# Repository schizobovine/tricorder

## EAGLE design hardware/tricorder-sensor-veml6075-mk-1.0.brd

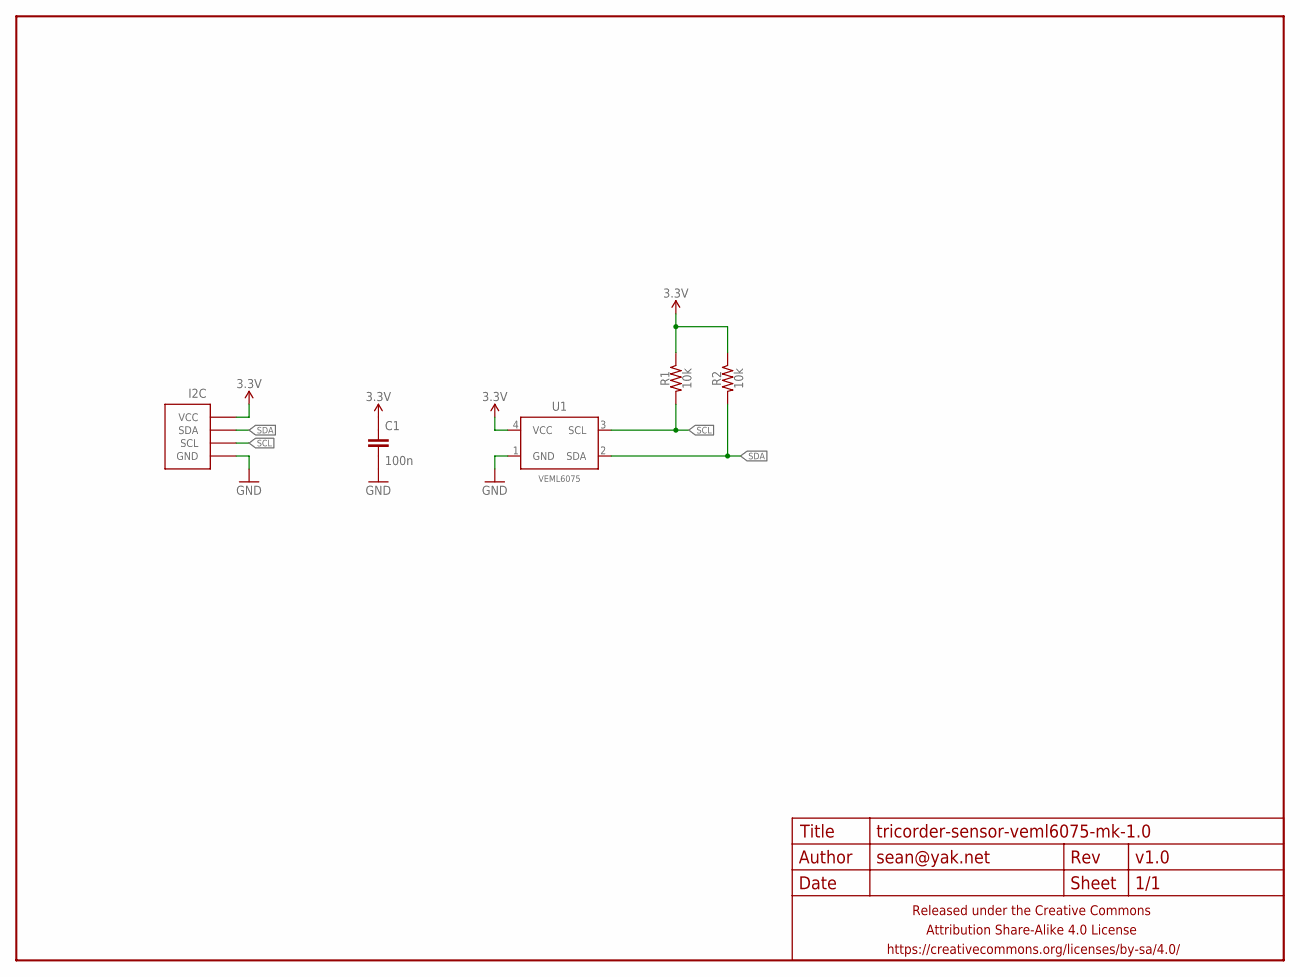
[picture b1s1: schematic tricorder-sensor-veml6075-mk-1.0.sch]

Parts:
C1: 100n; C0603
FRAME1: FRAME-LETTERNO_PACKAGE; DUMMY
I2C: M04-I2CPTH-0.1IN-CENTERED; 1X04-PTH-VERT-I2C-CENTERED
R1, R2: 10k; R0603
U1: VEML6075; OPLGA4

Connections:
3.3V: C1.1, I2C.VCC, R1.1, R2.1, U1.4 (VCC)
GND: C1.2, I2C.GND, U1.1 (GND)
SCL: I2C.SCL, R1.2, U1.3 (SCL)
SDA: I2C.SDA, R2.2, U1.2 (SDA)

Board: 2 copper layers, 6 parts (2 on the bottom side), 4 nets, no tracks yet.

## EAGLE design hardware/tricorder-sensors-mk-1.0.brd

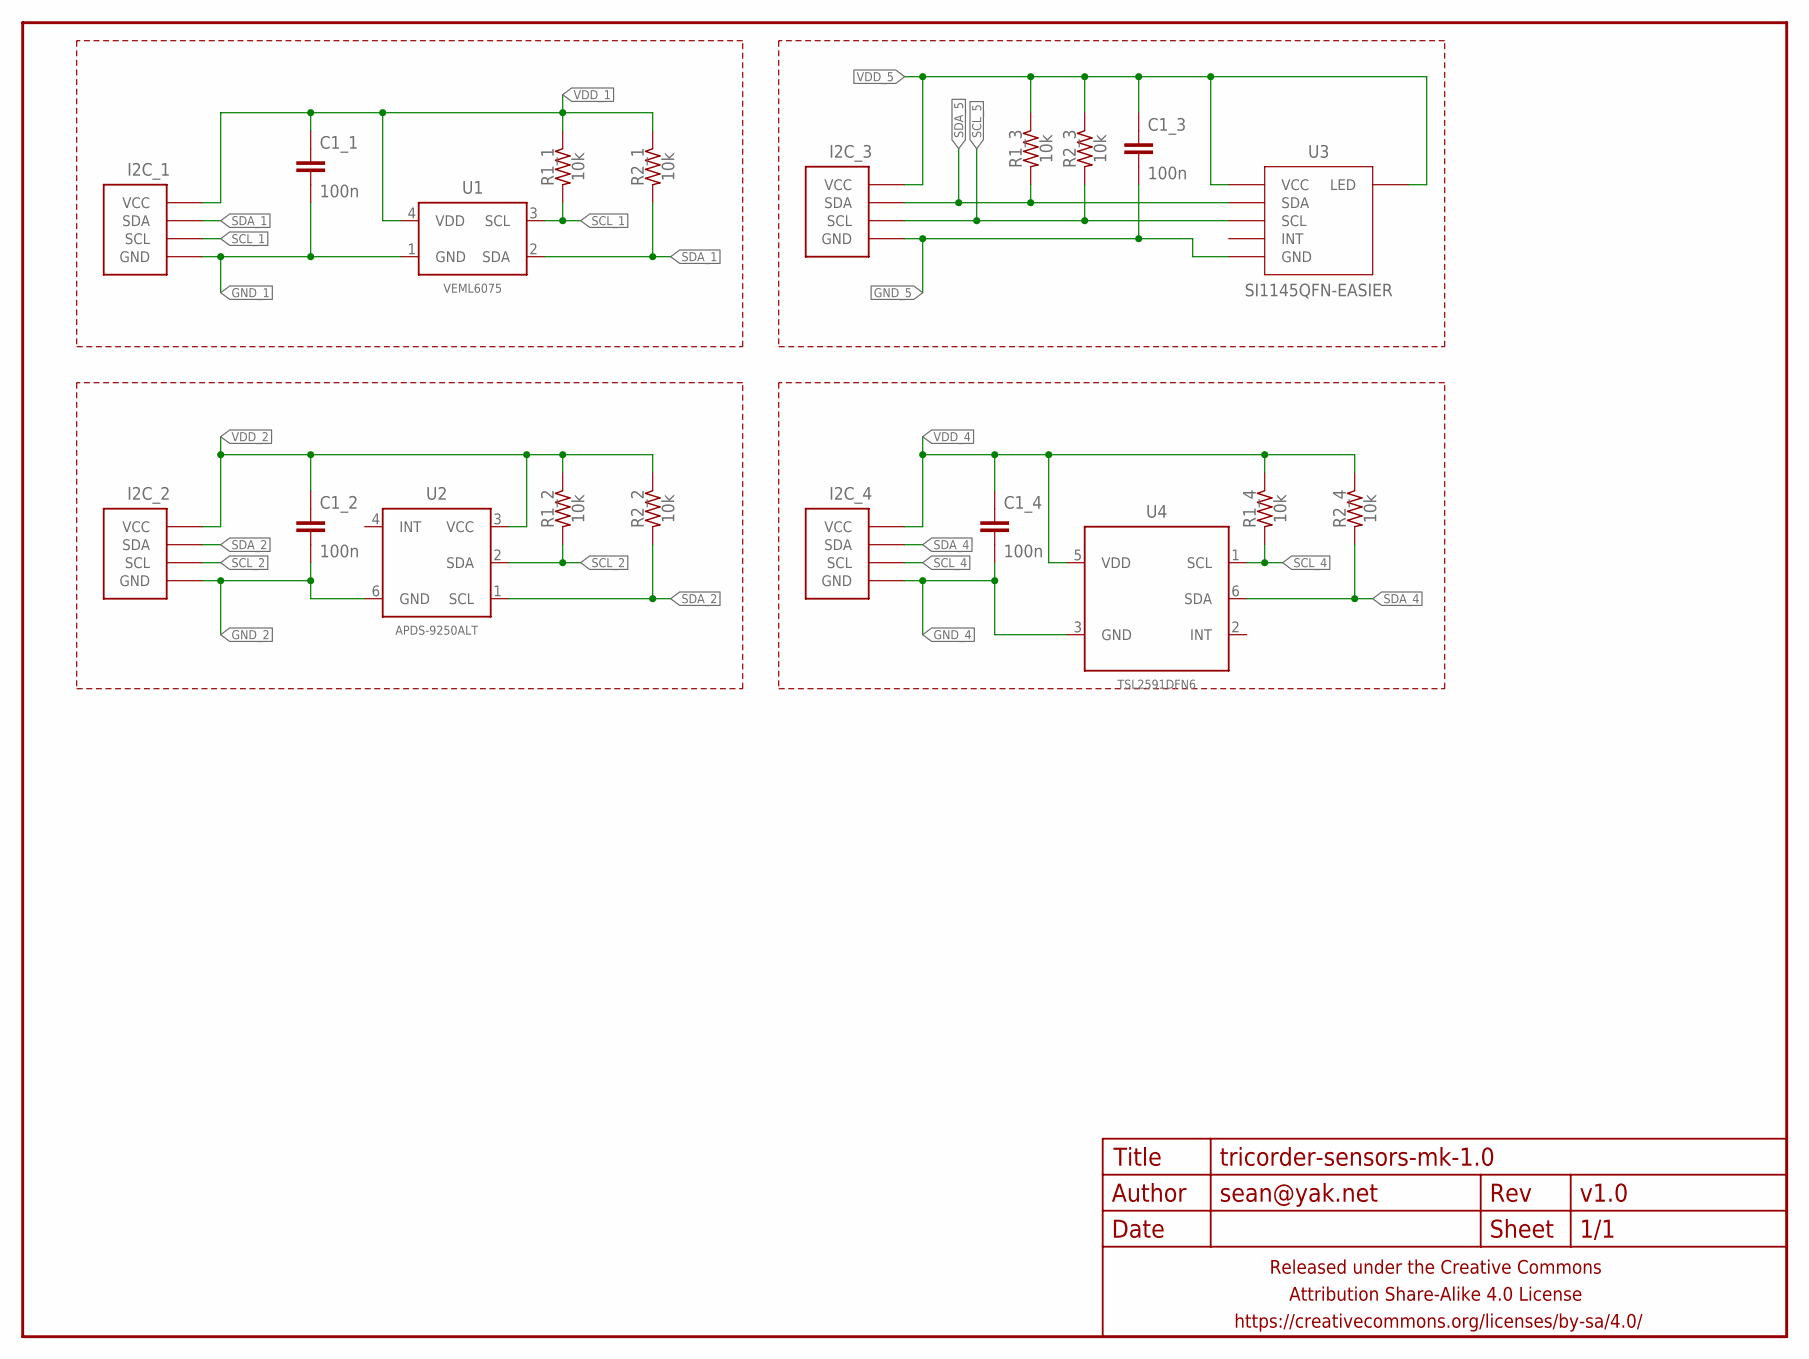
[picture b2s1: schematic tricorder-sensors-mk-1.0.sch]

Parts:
C1_1, C1_2, C1_3, C1_4: 100n; C0603
FRAME1: FRAME-LETTERNO_PACKAGE; DUMMY
I2C_1, I2C_2, I2C_3, I2C_4: M04-I2CPTH-0.1IN-CENTERED; 1X04-PTH-VERT-I2C-CENTERED
R1_1, R1_2, R1_3, R1_4, R2_1, R2_2, R2_3, R2_4: 10k; R0603
U1: VEML6075; OPLGA4
U2: APDS-9250ALT; APDS-9250-ALT
U3: SI1145QFN-EASIER; SI1145-ALT
U4: TSL2591DFN6; TSL2951_DFN6

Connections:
GND_1: C1_1.2, I2C_1.GND, U1.1 (GND)
GND_2: C1_2.2, I2C_2.GND, U2.6 (GND)
GND_4: C1_4.2, I2C_4.GND, U4.3 (GND)
GND_5: C1_3.2, I2C_3.GND, U3.GND
SCL_1: I2C_1.SCL, R1_1.2, U1.3 (SCL)
SCL_2: I2C_2.SCL, R1_2.2, U2.2 (SDA)
SCL_4: I2C_4.SCL, R1_4.2, U4.1 (SCL)
SCL_5: I2C_3.SCL, R2_3.2, U3.SCL
SDA_1: I2C_1.SDA, R2_1.2, U1.2 (SDA)
SDA_2: I2C_2.SDA, R2_2.2, U2.1 (SCL)
SDA_4: I2C_4.SDA, R2_4.2, U4.6 (SDA)
SDA_5: I2C_3.SDA, R1_3.2, U3.SDA
VDD_1: C1_1.1, I2C_1.VCC, R1_1.1, R2_1.1, U1.4 (VDD)
VDD_2: C1_2.1, I2C_2.VCC, R1_2.1, R2_2.1, U2.3 (VCC)
VDD_4: C1_4.1, I2C_4.VCC, R1_4.1, R2_4.1, U4.5 (VDD)
VDD_5: C1_3.1, I2C_3.VCC, R1_3.1, R2_3.1, U3.LED, U3.VCC@1 (VCC), U3.VCC@2 (VCC)

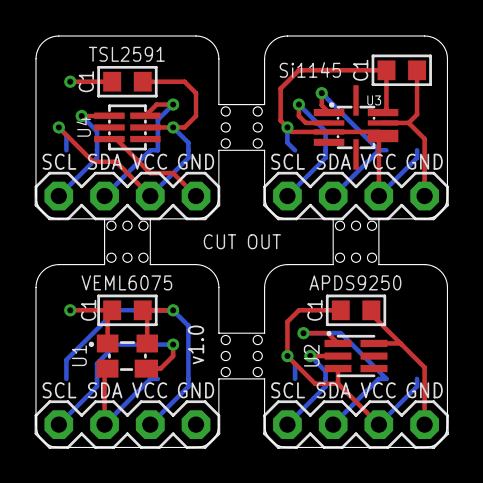
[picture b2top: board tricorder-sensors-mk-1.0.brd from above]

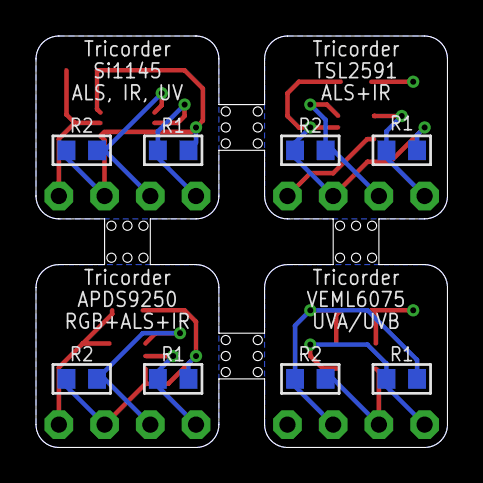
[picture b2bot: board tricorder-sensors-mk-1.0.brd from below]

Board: 2 copper layers, 22.9 x 22.9 mm, 21 parts (8 on the bottom side), 16 nets.

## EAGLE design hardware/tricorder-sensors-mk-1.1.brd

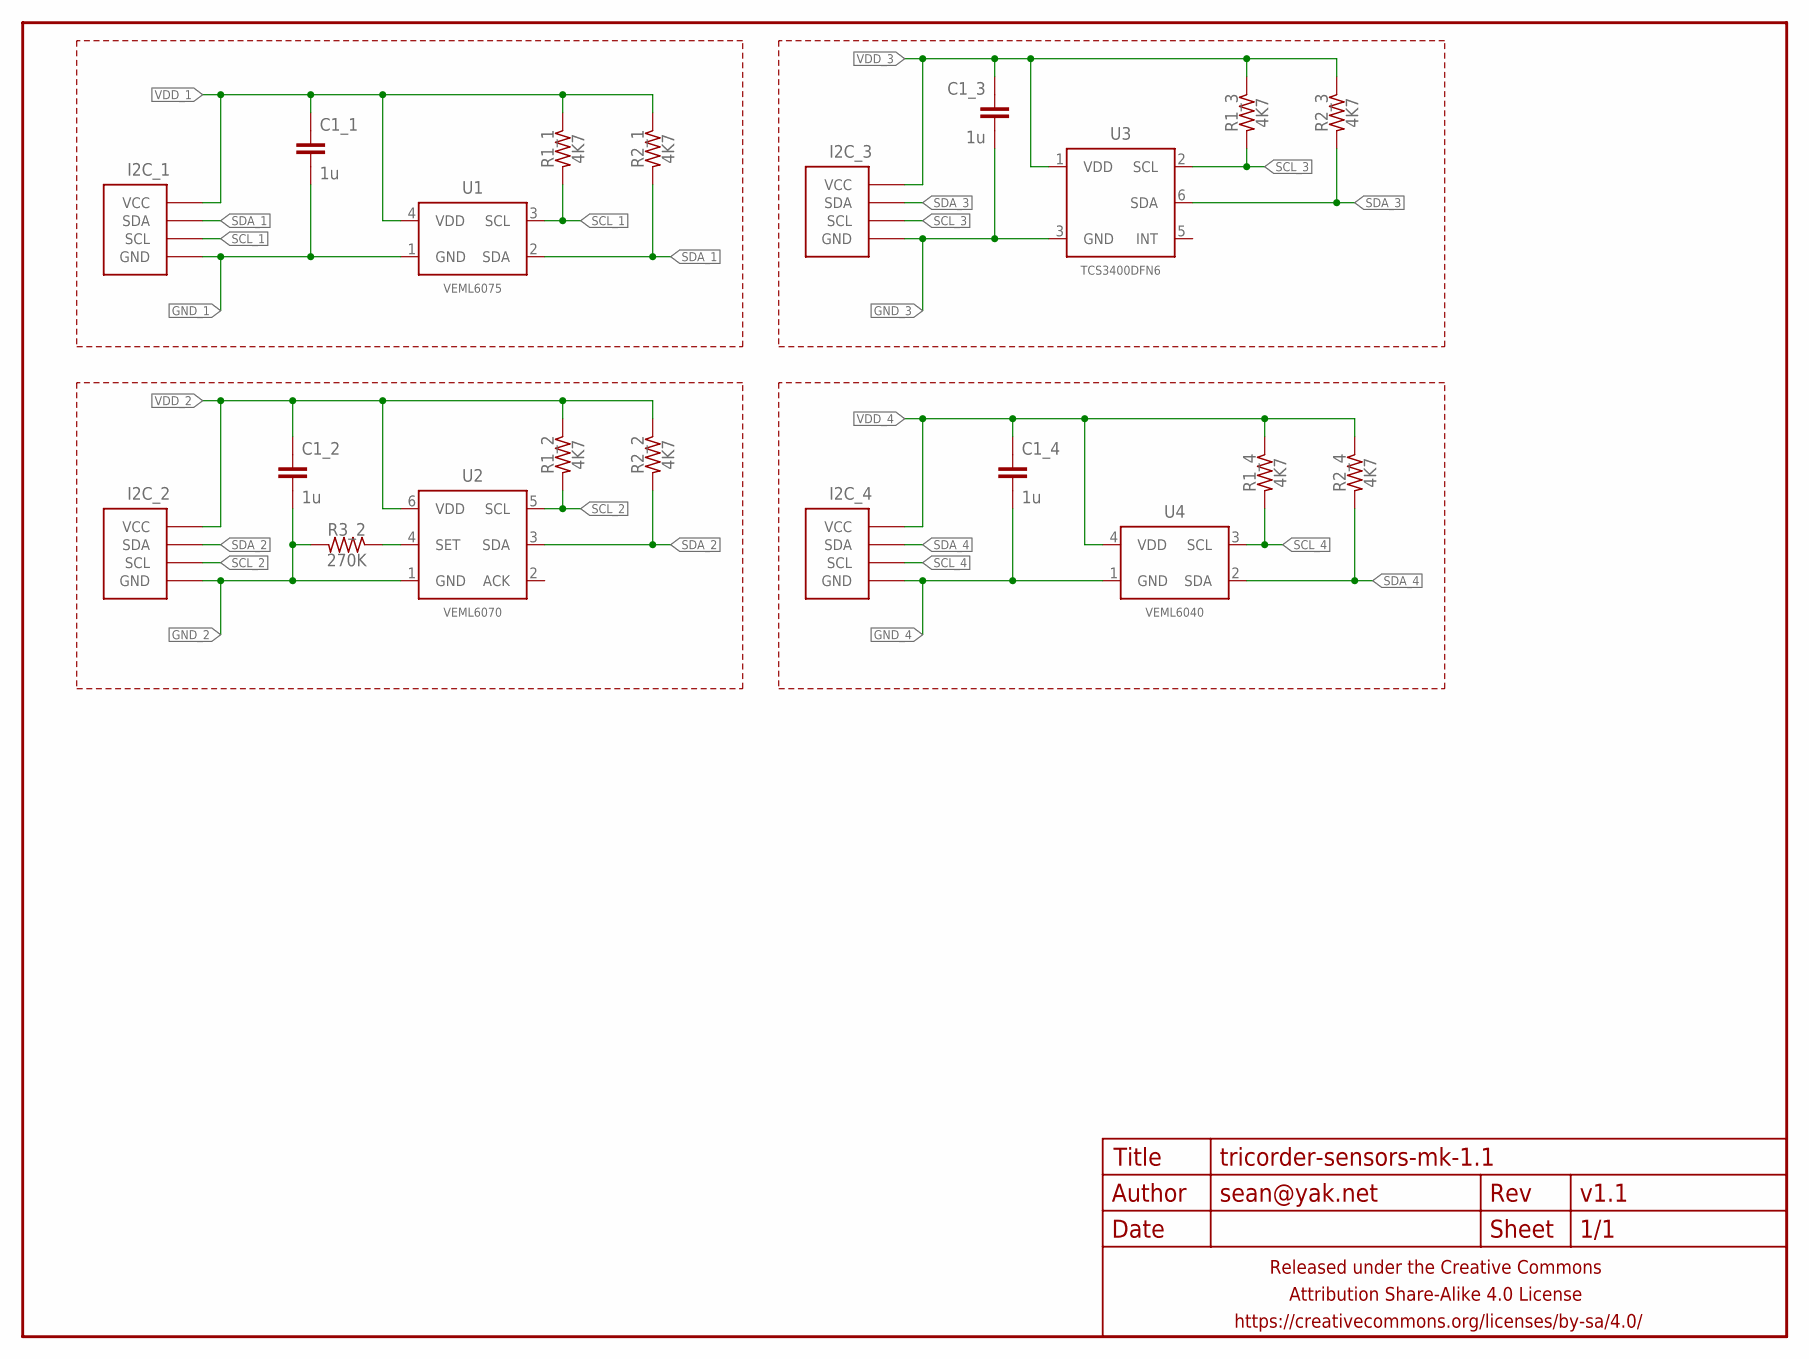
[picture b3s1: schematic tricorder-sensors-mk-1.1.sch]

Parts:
C1_1, C1_2, C1_3, C1_4: 1u; C0603
FRAME1: FRAME-LETTERNO_PACKAGE; DUMMY
I2C_1, I2C_2, I2C_3, I2C_4: M04-I2CPTH-0.1IN-CENTERED; 1X04-PTH-VERT-I2C-CENTERED
R1_1, R1_2, R1_3, R1_4, R2_1, R2_2, R2_3, R2_4: 4K7; R0603
R3_2: 270K; R0603
U1: VEML6075; OPLGA4
U2: VEML6070; OPLGA6
U3: TCS3400DFN6; TCS3400_DFN6
U4: VEML6040; OPLGA4

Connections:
GND_1: C1_1.2, I2C_1.GND, U1.1 (GND)
GND_2: C1_2.2, I2C_2.GND, R3_2.2, U2.1 (GND)
GND_3: C1_3.2, I2C_3.GND, U3.3 (GND)
GND_4: C1_4.2, I2C_4.GND, U4.1 (GND)
unnamed: R3_2.1, U2.4 (SET)
SCL_1: I2C_1.SCL, R1_1.2, U1.3 (SCL)
SCL_2: I2C_2.SCL, R1_2.2, U2.5 (SCL)
SCL_3: I2C_3.SCL, R1_3.2, U3.2 (SCL)
SCL_4: I2C_4.SCL, R1_4.2, U4.3 (SCL)
SDA_1: I2C_1.SDA, R2_1.2, U1.2 (SDA)
SDA_2: I2C_2.SDA, R2_2.2, U2.3 (SDA)
SDA_3: I2C_3.SDA, R2_3.2, U3.6 (SDA)
SDA_4: I2C_4.SDA, R2_4.2, U4.2 (SDA)
VDD_1: C1_1.1, I2C_1.VCC, R1_1.1, R2_1.1, U1.4 (VDD)
VDD_2: C1_2.1, I2C_2.VCC, R1_2.1, R2_2.1, U2.6 (VDD)
VDD_3: C1_3.1, I2C_3.VCC, R1_3.1, R2_3.1, U3.1 (VDD)
VDD_4: C1_4.1, I2C_4.VCC, R1_4.1, R2_4.1, U4.4 (VDD)

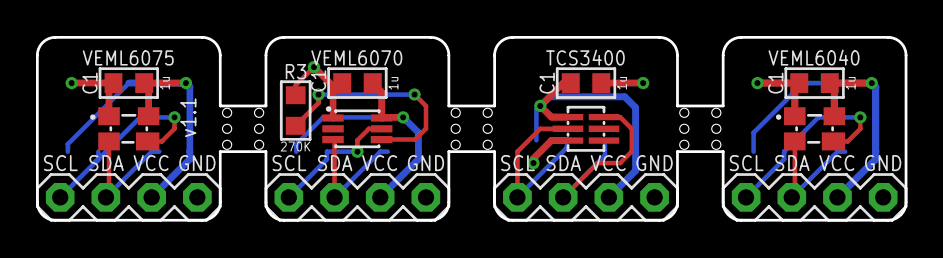
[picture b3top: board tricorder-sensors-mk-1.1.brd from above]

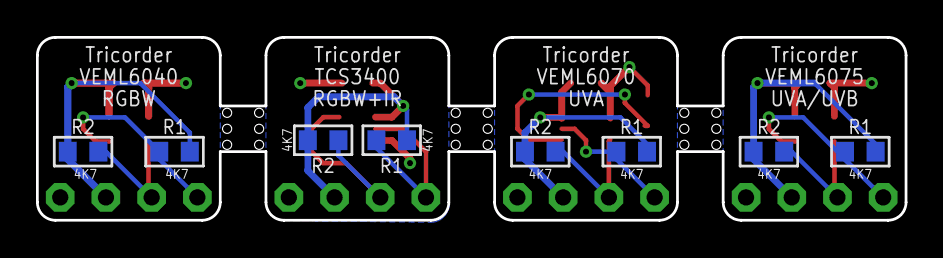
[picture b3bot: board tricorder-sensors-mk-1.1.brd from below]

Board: 2 copper layers, 48.3 x 10.2 mm, 22 parts (8 on the bottom side), 17 nets.

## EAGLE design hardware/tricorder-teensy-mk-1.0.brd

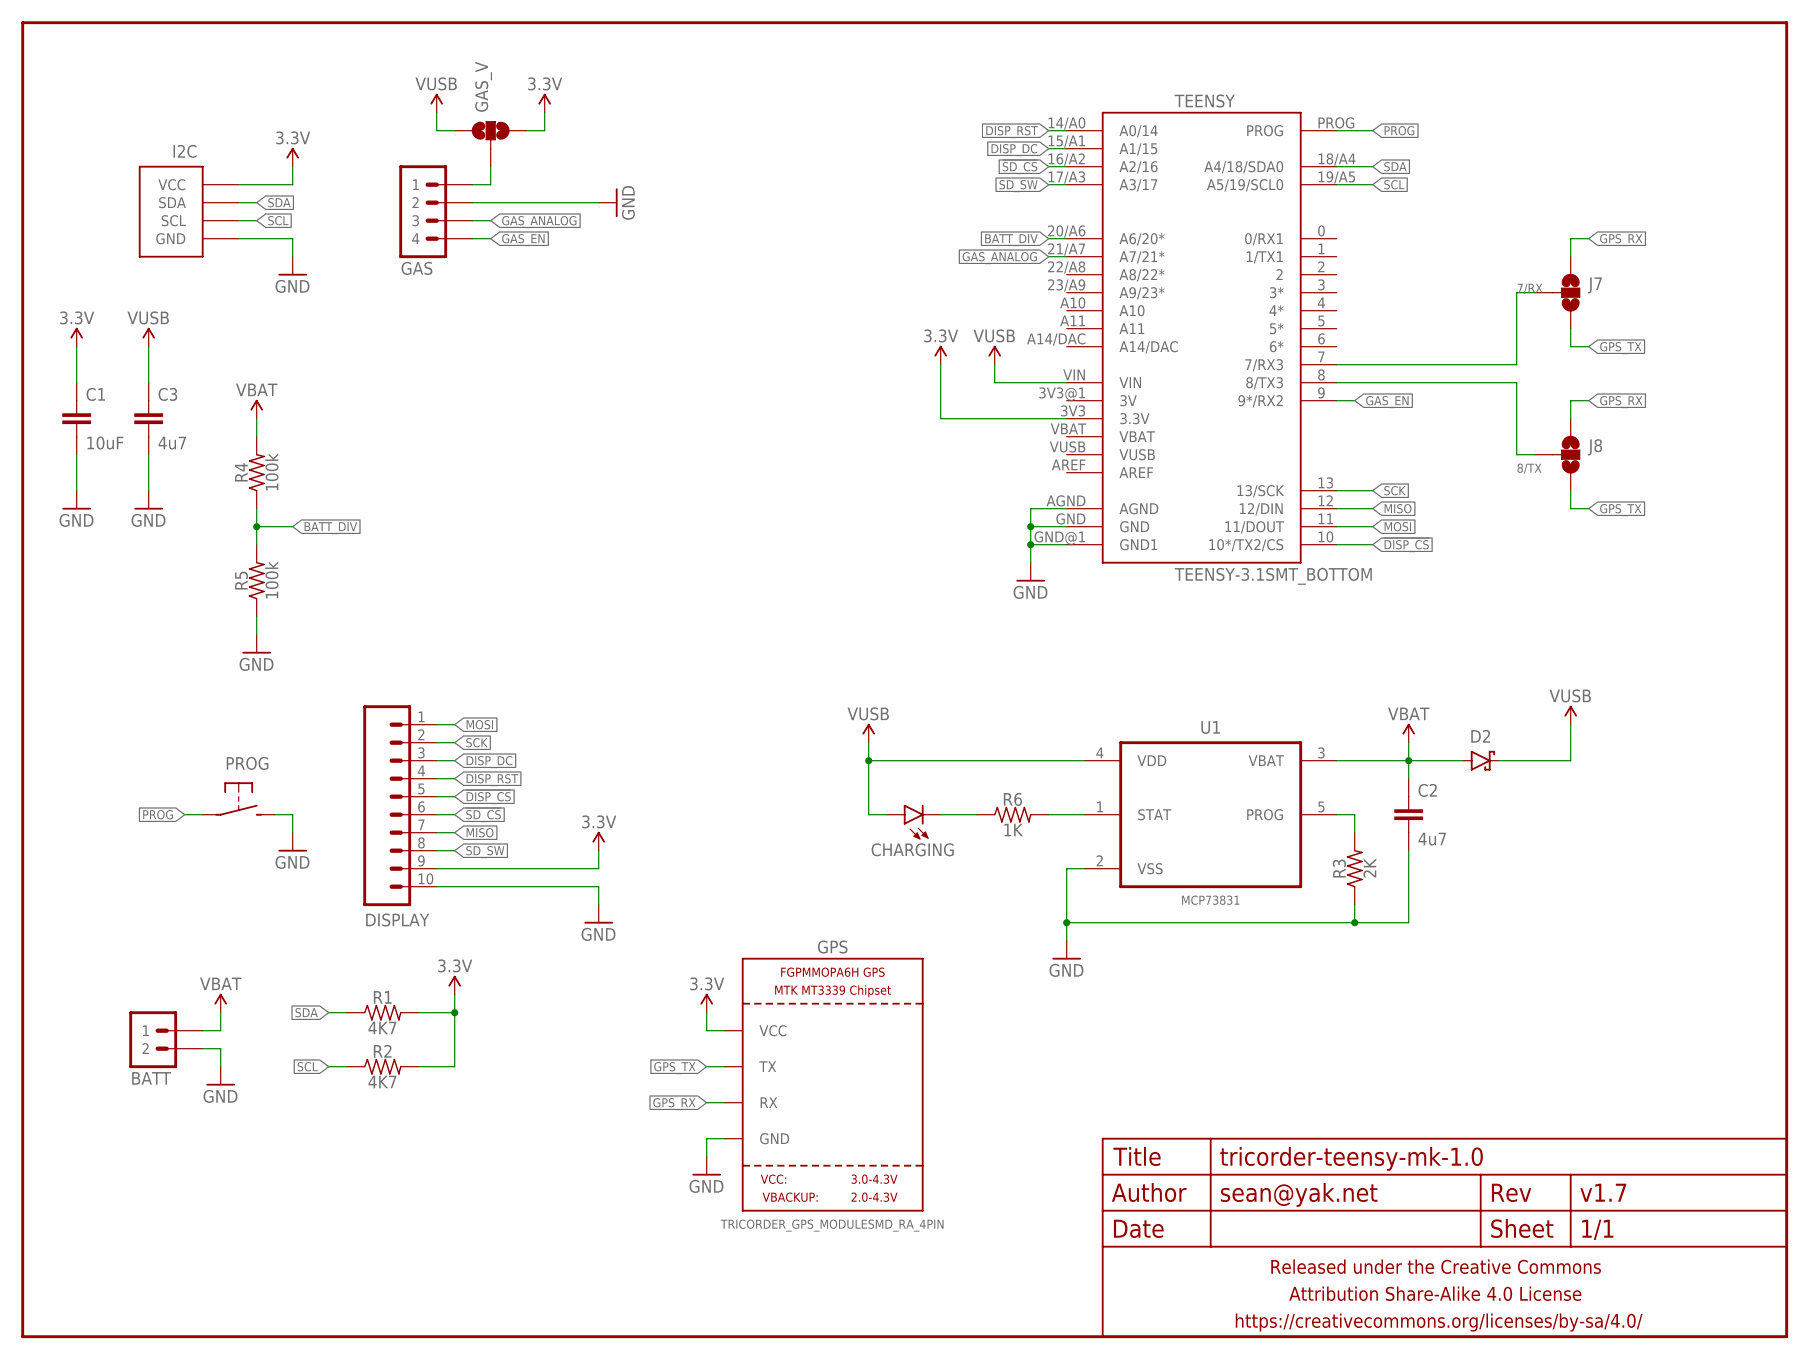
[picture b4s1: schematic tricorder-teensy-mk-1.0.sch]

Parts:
BATT: M02JST-2MM-SMT; JST-2-SMD
C1: 10uF; C0805-TIGHTER
C2, C3: 4u7; C0603-TIGHTER
CHARGING: LED0603-TIGHT; LED-0603-TIGHT
D2: DIODE-SCHOTTKYSOD323; SOD323-SCHOTTKY
DISPLAY: M10SMD_RA_2MM; 1X10_SMD_RA_MALE
FRAME1: FRAME-LETTERNO_PACKAGE; DUMMY
GAS: M04SMD_RA_2MM; 1X04_SMD_RA_2MM
GAS_V: JUMPER-PAD-3-NOFULL_BOX_SILK; PAD-JUMPER-3-NO_YES_SILK_FULL_BOX
GPS: TRICORDER_GPS_MODULESMD_RA_4PIN; TRICORDER_GPS_MODULE_RA_CONN_SMD_4PIN
I2C: M04-I2CSMD_2MM_RA; 1X04_SMD_RA_2MM_I2C
J7, J8: JUMPER-PAD-3-NOFULL_BOX_SILK; PAD-JUMPER-3-NO_YES_SILK_FULL_BOX
PROG: SPST-NO-TACTCK-PTS840-GK; TACTILE-SMD-CK-PTS840-GK
R1, R2: 4K7; R0603-TIGHTER
R3: 2K; R0603-TIGHTER
R4, R5: 100k; R0603-TIGHTER
R6: 1K; R0603-TIGHTER
TEENSY: TEENSY-3.1SMT_BOTTOM; TEENSY-3.1_SMT_BOTTOM
U1: MCP73831; SOT95P280X145-5N

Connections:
3.3V: C1.1, DISPLAY.9, GAS_V.3, GPS.VCC, I2C.VCC, R1.2, R2.2, TEENSY.3V3 (3.3V)
7/RX: J7.2, TEENSY.7 (7/RX3)
8/TX: J8.2, TEENSY.8 (8/TX3)
!DISP_CS: DISPLAY.5, TEENSY.10 (10*/TX2/CS)
!SD_CS: DISPLAY.6, TEENSY.16/A2 (A2/16)
BATT_DIV: R4.1, R5.2, TEENSY.20/A6 (A6/20*)
DISP_DC: DISPLAY.3, TEENSY.15/A1 (A1/15)
DISP_RST: DISPLAY.4, TEENSY.14/A0 (A0/14)
GAS_ANALOG: GAS.3, TEENSY.21/A7 (A7/21*)
GAS_EN: GAS.4, TEENSY.9 (9*/RX2)
GND: BATT.1 (2), C1.2, C2.2, C3.2, DISPLAY.10, GAS.2, GPS.GND, I2C.GND, PROG.3 (2), PROG.4 (2), R3.1, R5.1, TEENSY.AGND, TEENSY.GND, TEENSY.GND@1 (GND1), U1.2 (VSS)
GPS_RX: GPS.RX, J7.1, J8.1
GPS_TX: GPS.TX, J7.3, J8.3
MISO: DISPLAY.7, TEENSY.12 (12/DIN)
MOSI: DISPLAY.1, TEENSY.11 (11/DOUT)
unnamed: R6.2, U1.1 (STAT)
unnamed: CHARGING.C, R6.1
unnamed: GAS.1, GAS_V.2
unnamed: R3.2, U1.5 (PROG)
PROG: PROG.1, PROG.2 (1), TEENSY.PROG
SCK: DISPLAY.2, TEENSY.13 (13/SCK)
SCL: I2C.SCL, R2.1, TEENSY.19/A5 (A5/19/SCL0)
SDA: I2C.SDA, R1.1, TEENSY.18/A4 (A4/18/SDA0)
SD_SW: DISPLAY.8, TEENSY.17/A3 (A3/17)
VBAT: BATT.2 (1), C2.1, D2.A, R4.2, U1.3 (VBAT)
VUSB: C3.1, CHARGING.A, D2.C, GAS_V.1, TEENSY.VIN, U1.4 (VDD)

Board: 2 copper layers, 24 parts (6 on the bottom side), 26 nets, no tracks yet.

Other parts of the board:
U$2: COW_SMALL_METAL

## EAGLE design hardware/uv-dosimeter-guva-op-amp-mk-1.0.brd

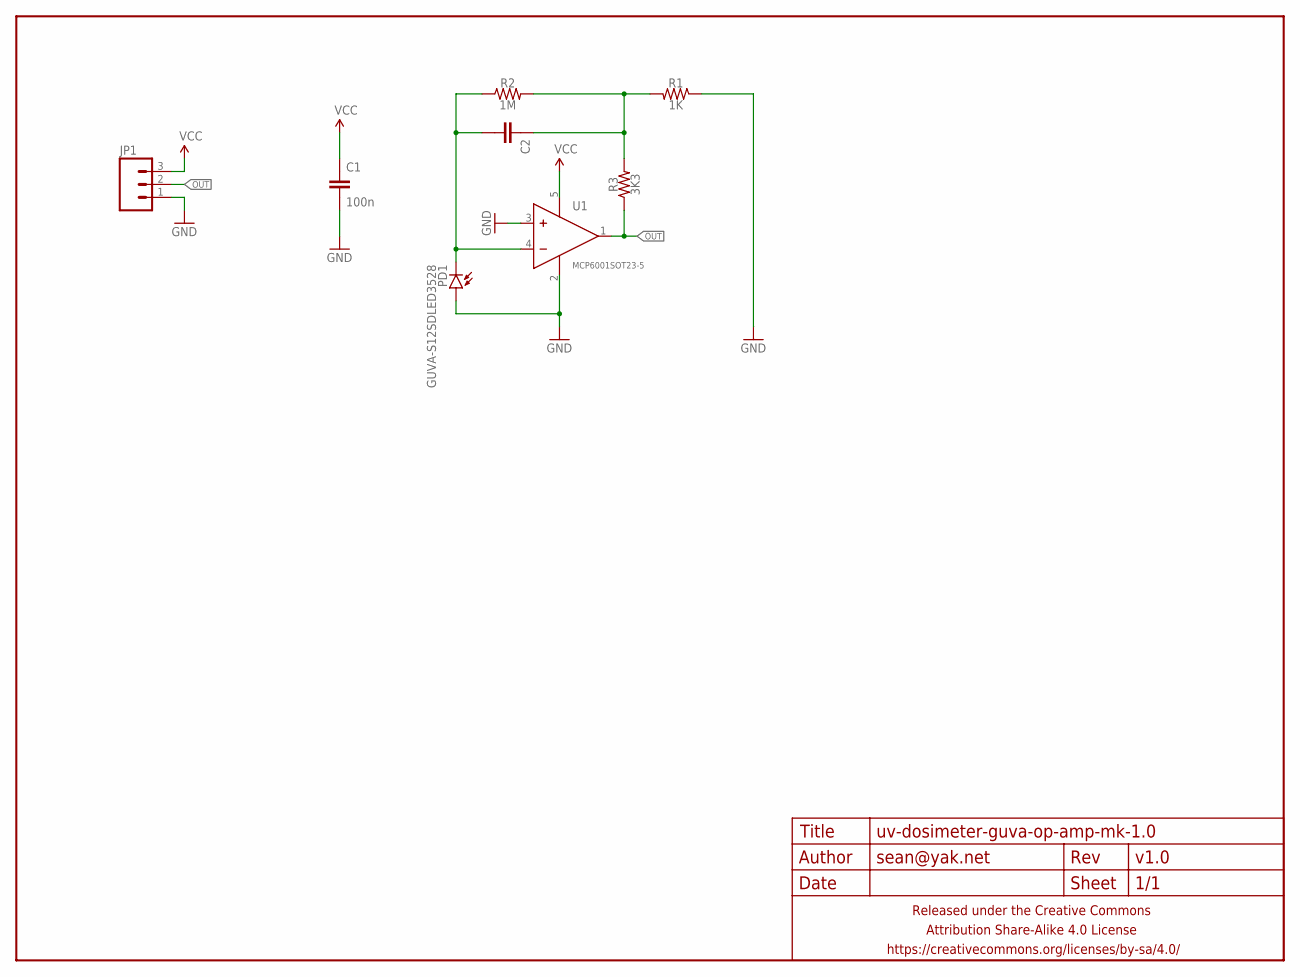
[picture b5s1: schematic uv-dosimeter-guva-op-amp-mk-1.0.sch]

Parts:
C1: 100n; C0603
C2: CAPACITOR-CERAMICC0603; C0603
FRAME1: FRAME-LETTERNO_PACKAGE; DUMMY
JP1: M03PTH-CENTERED; 1X03-CENTERED
PD1: GUVA-S12SDLED3528; LED3528
R1: 1K; R0603
R2: 1M; R0603
R3: 3K3; R0603
U1: MCP6001SOT23-5; SOT23-5

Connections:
GND: C1.2, JP1.1, PD1.A, R1.1, U1.2 (V-), U1.3 (IN+)
unnamed: C2.1, R1.2, R2.2, R3.2
unnamed: C2.2, PD1.K (C), R2.1, U1.4 (IN-)
OUT: JP1.2, R3.1, U1.1 (OUT)
VCC: C1.1, JP1.3, U1.5 (V+)

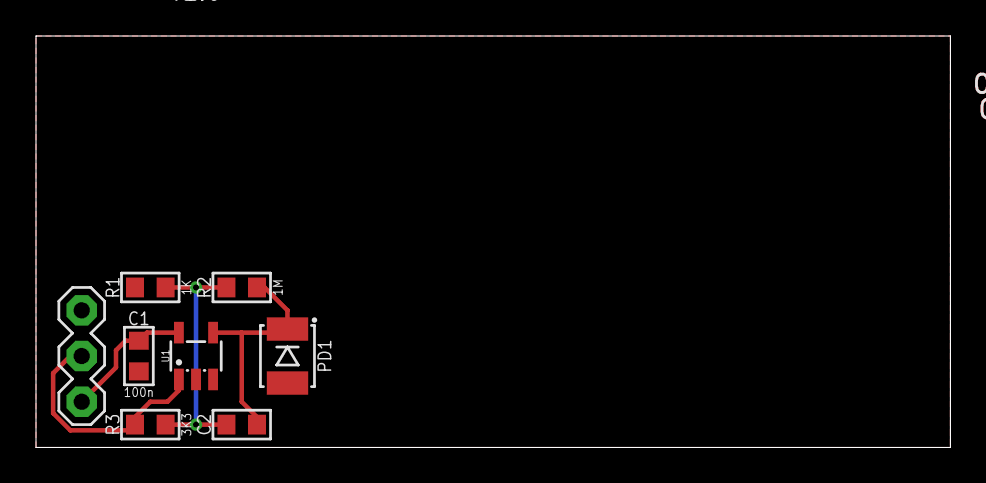
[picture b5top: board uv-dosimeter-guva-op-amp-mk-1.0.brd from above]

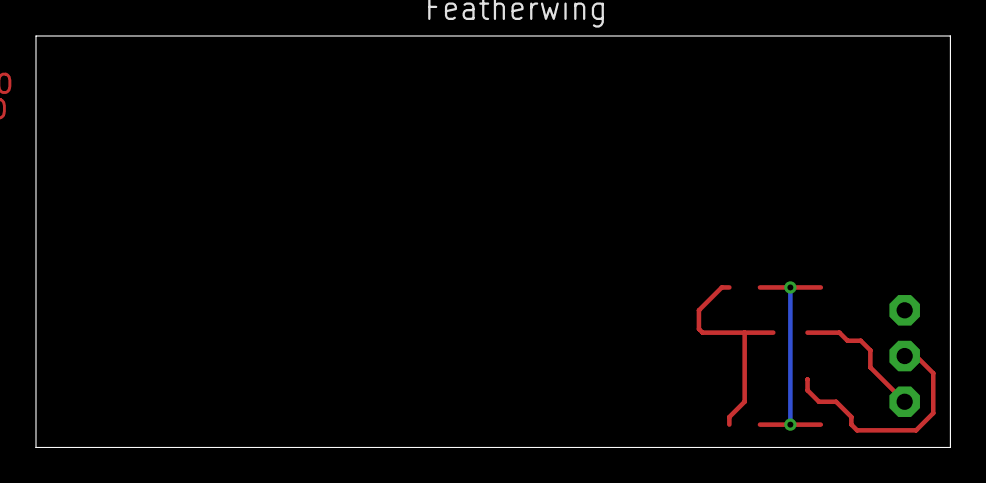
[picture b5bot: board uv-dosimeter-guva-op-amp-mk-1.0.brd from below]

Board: 2 copper layers, 50.8 x 22.9 mm, 11 parts (3 on the bottom side), 5 nets.

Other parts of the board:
U$1: COW_SMALL
U$5: CC-BY-SA-4.0-NO-URL

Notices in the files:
parts and their libraries:
a_parts: Released under the Creative Commons Attribution Share-Alike 4.0 License
a_parts: https://creativecommons.org/licenses/by-sa/4.0
a_parts: Released under the Creative Commons
